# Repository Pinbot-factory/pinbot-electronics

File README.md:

**Pinbot** is an open-source platform for quickly building test jigs for electronics QA. The platform is made up of [mechanical fixture](https://github.com/Pinbot-factory/pinbot-mechanical), control electronics (this repo), jig-level software and backend to store all test results.

## Pinbot electronics
This repo is dedicated for electronics of a typical Pinbot jig. At a moment it is a compact carrier board for Raspberry Pi Zero [2](https://www.jeffgeerling.com/blog/2021/look-inside-raspberry-pi-zero-2-w-and-rp3a0-au/). The board also can be used with regular size RPis thru HAT connector (J3).

**It features:**
- 16 channels GPIO (0-24V) thru TCA9535
- 8 channels ADC (12 bit, 0-24V) thru ADS1015
- 4 signal relays
- USB hub
    - 4 downstream ports (3 USB-A + 1 as a pins on J2)
    - Per-port power control
    - Per-port fault signals for error and power failures handling
- Qwiic connector for easy I2C expansion
- Raspberry Pi 40-pin GPIO header with SPI, I2C, UART, etc
- USB-C for power supply
- User leds, test points, basic signal lines protection and more.

Carrier board is 114x65mm to fit perfectly into [Pinbot's chassis](https://github.com/Pinbot-factory/pinbot-mechanical/tree/main/chassis). You can use it as a test engine for a small projects and supply them (as well as connected USB periphery) with 5V.

The repo includes KiCAD source files, generated gerbers, BOM, and everything to produce it on your own. Python *library and software examples* are also available and briefly [documented](sw_examples/README.md).

## License
- [GNU GPLv3](https://www.gnu.org/licenses/gpl-3.0.en.html) for **software**: firmware, libraries, generators, tools, examples, etc
- [CERN-OHL-S](https://cern-ohl.web.cern.ch/) for **hardware**: PCB schematic, layout, BOM, gerbers, 3D models, g-codes, etc.
- [CC BY-SA 4.0](https://creativecommons.org/licenses/by-sa/4.0/deed.en) is for docs, pictures, articles, video, assets, etc.

Pinbot projects structure may mix different sources and artifacts — check corresponding dirrectories for `LICENSE` file.

-----------
*This project is sponsored by [NLnet](https://nlnet.nl/) as a part of [NGI Zero Review](https://nlnet.nl/NGI0/review/) program.*
<p align="left">
    
</p>

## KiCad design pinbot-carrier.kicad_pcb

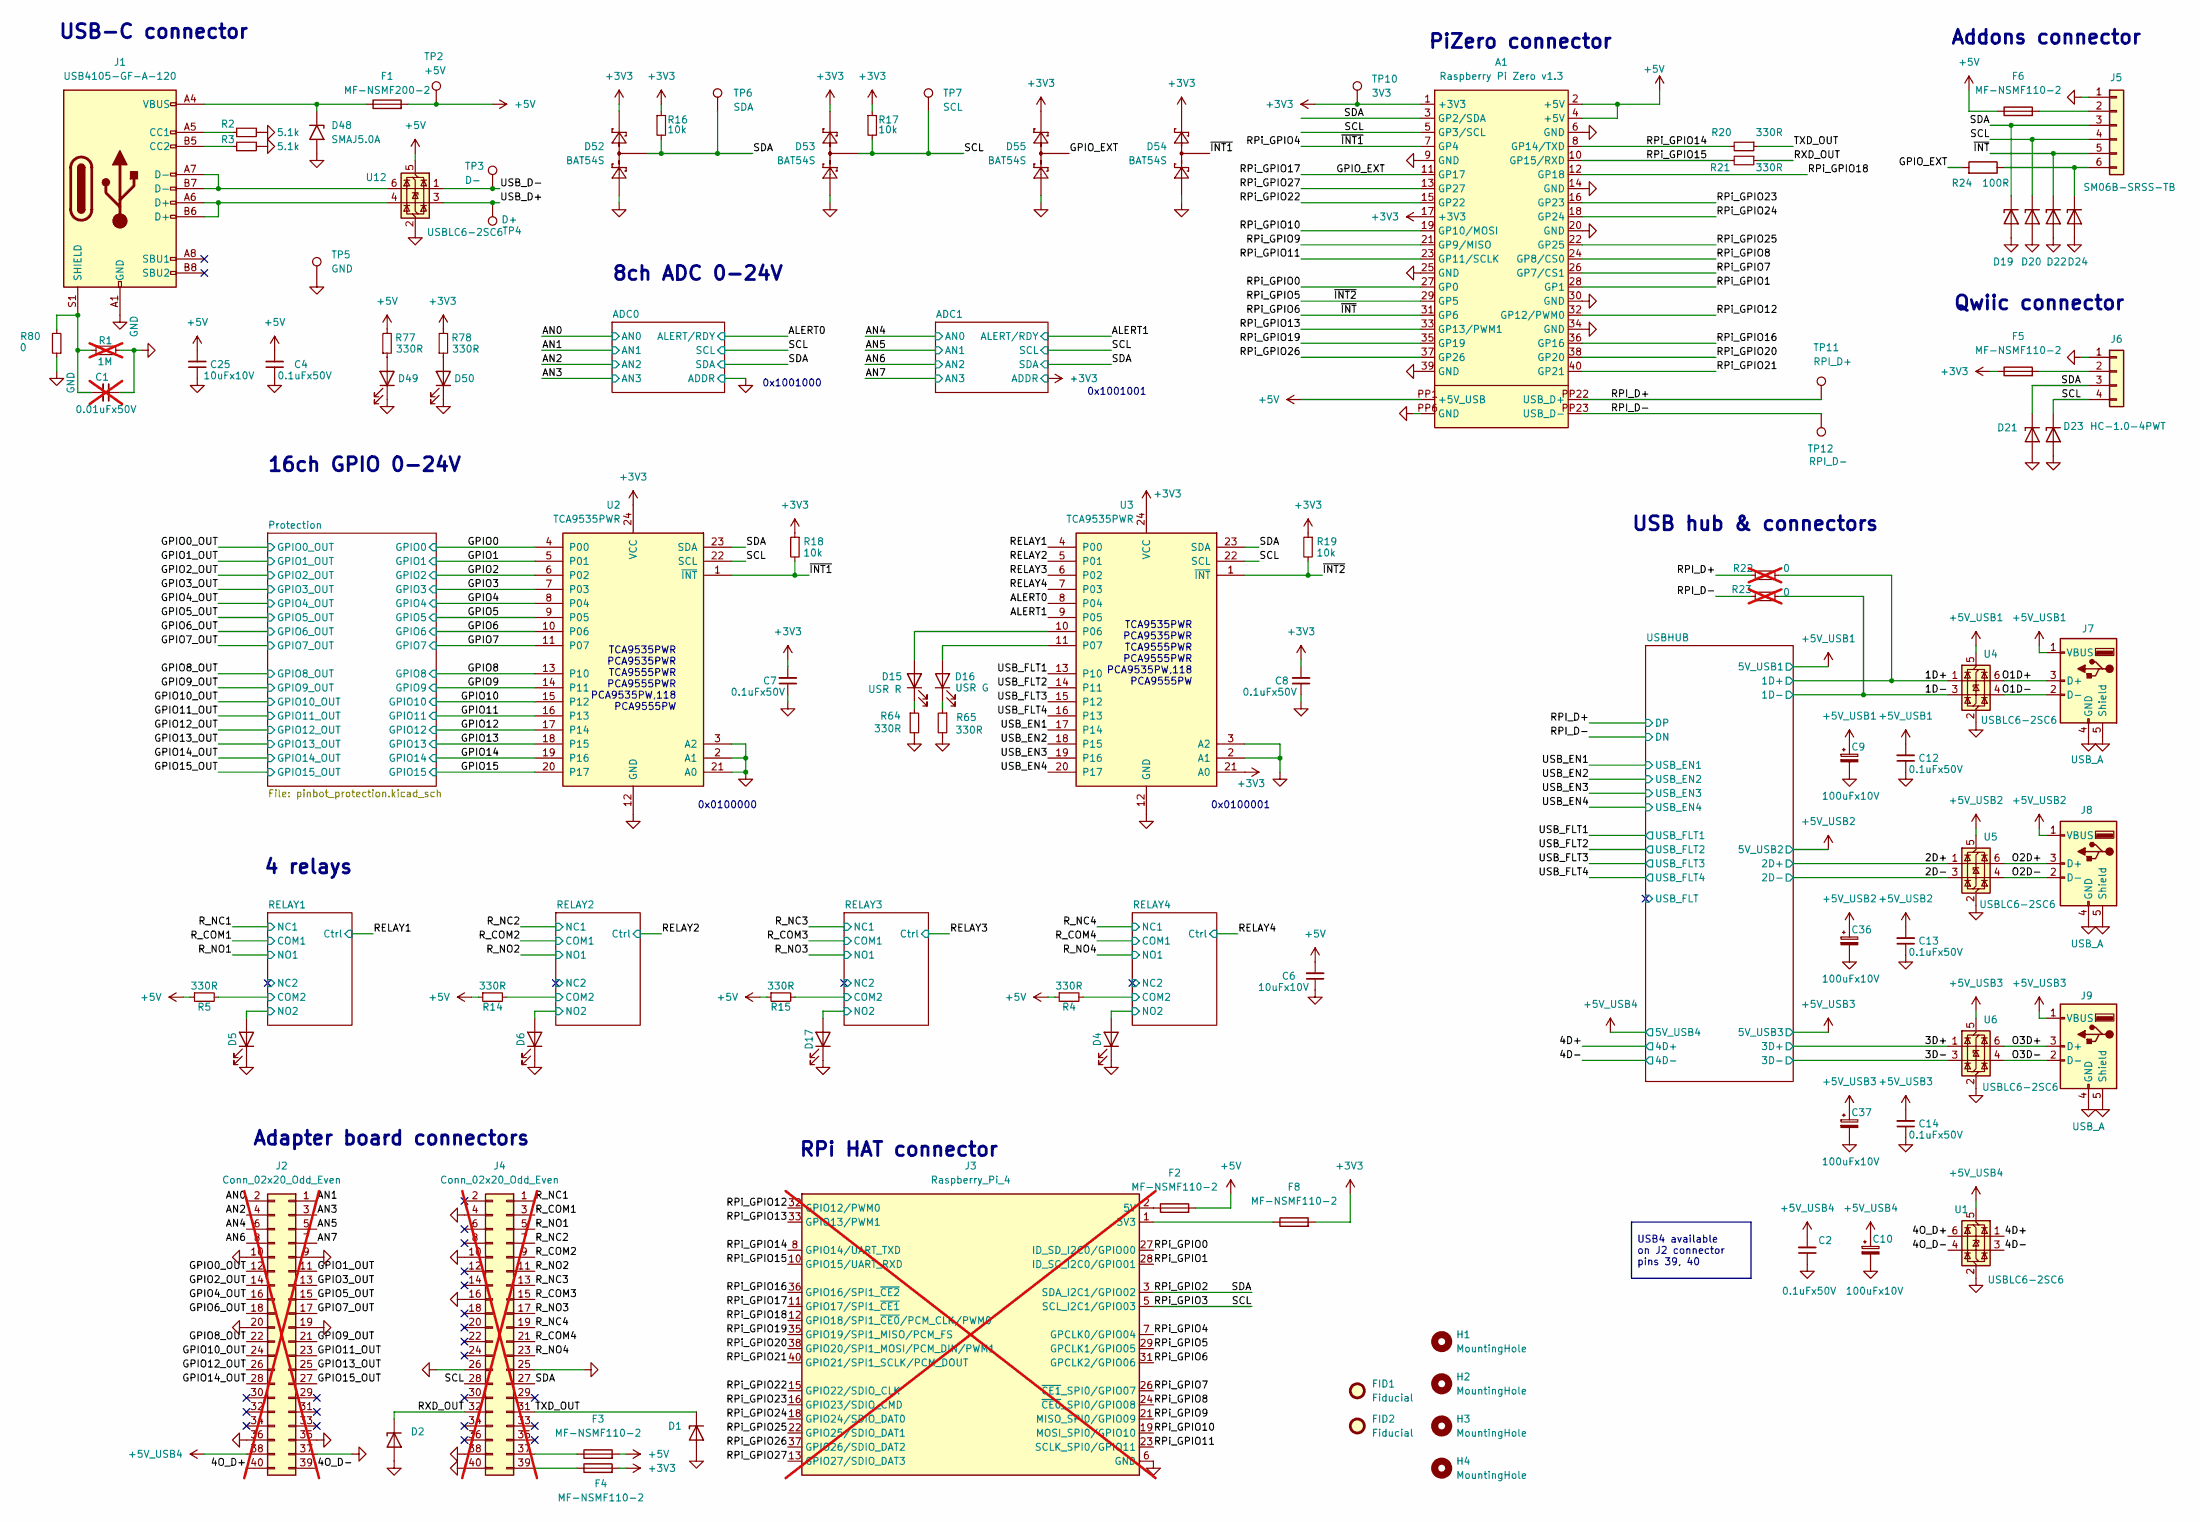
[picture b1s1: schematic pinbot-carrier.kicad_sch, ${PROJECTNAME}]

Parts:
A1: Raspberry Pi Zero v1.3; RASPI_ZERO_FULL; LCSC Part # C2977589
C1: 0.01uFx50V; C_0603_1608Metric; Mouser Part # 06031C103K4T4A; LCSC Part # C100042; not fitted
C2, C4, C12, C13, C14: 0.1uFx50V; C_0603_1608Metric; Mouser Part # CGA3E2X7R1H104M080AA; LCSC Part # C282519
C6, C25: 10uFx10V; C_0603_1608Metric; Mouser Part # GRM188Z71A106MA73J; LCSC Part # C2959727
C7, C8: 0.1uFx50V; C_0603_1608Metric; Mouser Part # CGA3E2X7R1H104M080AA
C9, C10, C36, C37: 100uFx10V; CP_EIA-3528-21_Kemet-B; LCSC Part # C600583
D1, D2, D19, D20, D21, D22, D23, D24: ESD5Z3.3T5G; D_SOD-523; Mouser Part # ESD5Z3.3T5G
D4, D5, D6, D17: 19-21/GHC-YR1S2/4T; LED_0603_1608Metric; LCSC Part # C2986048
D15: LTST-S270KRKT; LED_0603_1608Metric_side; Mouser Part # LTST-S270KRKT; LCSC Part # C125114
D16: LTST-S270KGKT; LED_0603_1608Metric_side; Mouser Part # LTST-S270KGKT; LCSC Part # C125113
D48: SMAJ5.0A; D_SMA; LCSC Part # C83329
D49, D50: XL-1608SURC-06; LED_0603_1608Metric; LCSC Part # C965799
D52, D53, D54, D55: BAT54S; SOT-23; LCSC Part # C19726
F1: MF-NSMF200-2; Fuse_1206_3216Metric; Mouser Part # MF-NSMF200-2; LCSC Part # C89656
F2, F3, F4, F5, F6, F8: MF-NSMF110-2; Fuse_1206_3216Metric; Mouser Part # MF-NSMF110-2; LCSC Part # C89654
FID1, FID2: Fiducial; Fiducial_1mm_Mask2mm
H1, H2, H3, H4: MountingHole; MountingHole_2.7mm
J1: USB4105-GF-A-120; USB_C_Receptacle_GCT_USB4105-xx-A_16P_TopMnt_Horizontal; Mouser Part # USB4105-GF-A-120
J2: Conn_02x20_Odd_Even; PinHeader_2x20_P2.54mm_Horizontal; LCSC Part # C124369; not fitted
J3: Raspberry_Pi_4; PinHeader_2x20_P2.54mm_Vertical; Manufacturer Part P125-1220A0BS116A1; LCSC Part # C19190512; not fitted
J4: Conn_02x20_Odd_Even; PinHeader_2x20_P2.54mm_Vertical; LCSC Part # C19190512; not fitted
J5: SM06B-SRSS-TB; JST_SM06B-SRSS-TB; Mouser Part # 10147606-00006LF; LCSC Part # C160405
J6: HC-1.0-4PWT; JST_SH_SM04B-SRSS-TB_1x04-1MP_P1.00mm_Horizontal; Mouser Part # 10147606-00004LF; LCSC Part # C2845363
J7, J8, J9: USB_A; GCT_USB1125-GF-B_REVA; Mouser Part # USB1125-GF-B
R1: 1M; R_0603_1608Metric; Mouser Part # ASC0603-1M0FT5; LCSC Part # C107698; not fitted
R2, R3: 5.1k; R_0603_1608Metric; Mouser Part # ERJ-3EKF5101V; LCSC Part # C2907114
R4, R5, R14, R15, R20, R21, R64, R65, R77, R78: 330R; R_0603_1608Metric; Mouser Part # RMCF0603FT330R; LCSC Part # C23138
R16, R17, R18, R19: 10k; R_0603_1608Metric; Mouser Part # RMC1/16K1002DTP; LCSC Part # C98220
R22, R23: 0; R_0603_1608Metric; Mouser Part # ERJ-3EKF5101V; LCSC Part # C95177; not fitted
R24: 100R; R_0603_1608Metric; Mouser Part # CRT0603-DY-1000ELF; LCSC Part # C2907089
R80: 0; R_0603_1608Metric; Mouser Part # ERJ-3EKF5101V; LCSC Part # C95177
TP2: +5V; TestPoint_Loop_D1.80mm_Drill1.0mm_Beaded
TP3: D-; TestPoint_Loop_D1.80mm_Drill1.0mm_Beaded
TP4: D+; TestPoint_Loop_D1.80mm_Drill1.0mm_Beaded
TP5: GND; TestPoint_Loop_D1.80mm_Drill1.0mm_Beaded
TP6: SDA; TestPoint_Loop_D1.80mm_Drill1.0mm_Beaded
TP7: SCL; TestPoint_Loop_D1.80mm_Drill1.0mm_Beaded
TP10: 3V3; TestPoint_Loop_D1.80mm_Drill1.0mm_Beaded
TP11: RPI_D+; TestPoint_Loop_D1.80mm_Drill1.0mm_Beaded
TP12: RPI_D-; TestPoint_Loop_D1.80mm_Drill1.0mm_Beaded
U1, U4, U5, U6, U12: USBLC6-2SC6; SOT-23-6; Mouser Part # USBLC6-2SC6
U2, U3: TCA9535PWR; TSSOP-24_4.4x7.8mm_P0.65mm; Mouser Part # TCA9535PWR

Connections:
+3V3: A1.1 (+3V3), A1.17 (+3V3), C7.2, C8.2, D52.2 (K), D53.2 (K), D54.2 (K), D55.2 (K), F4.2, F5.1, F8.2, R16.1, R17.1, R18.1, R19.1, R78.2, TP10.1 (1_1), U2.24 (VCC), U3.21 (A0), U3.24 (VCC); also elsewhere on the board
+5V: A1.2 (+5V), A1.4 (+5V), A1.PP1 (+5V_USB), C4.2, C6.2, C25.2, F1.2, F2.2, F3.2, F6.1, R4.1, R5.1, R14.1, R15.1, R77.2, TP2.1 (1_1), U12.5 (VBUS); also elsewhere on the board
+5V_USB1: C9.1, C12.2, J7.1 (VBUS), U4.5 (VBUS); also elsewhere on the board
+5V_USB2: C13.2, C36.1, J8.1 (VBUS), U5.5 (VBUS); also elsewhere on the board
+5V_USB3: C14.2, C37.1, J9.1 (VBUS), U6.5 (VBUS); also elsewhere on the board
+5V_USB4: C2.2, C10.1, J2.38, U1.5 (VBUS); also elsewhere on the board
/1D+: R22.2, U4.1 (I/O1); also elsewhere on the board
/1D-: R23.2, U4.3 (I/O2); also elsewhere on the board
/2D+: U5.1 (I/O1); also elsewhere on the board
/2D-: U5.3 (I/O2); also elsewhere on the board
/3D+: U6.1 (I/O1); also elsewhere on the board
/3D-: U6.3 (I/O2); also elsewhere on the board
/4D+: U1.1 (I/O1); also elsewhere on the board
/4D-: U1.3 (I/O2); also elsewhere on the board
/4O_D+: J2.40, U1.6 (I/O1)
/4O_D-: J2.39, U1.4 (I/O2)
/ALERT0: U3.8 (P04); also elsewhere on the board
/ALERT1: U3.9 (P05); also elsewhere on the board
/AN0: J2.2; also elsewhere on the board
/AN1: J2.1; also elsewhere on the board
/AN2: J2.4; also elsewhere on the board
/AN3: J2.3; also elsewhere on the board
/AN4: J2.6; also elsewhere on the board
/AN5: J2.5; also elsewhere on the board
/AN6: J2.8; also elsewhere on the board
/AN7: J2.7; also elsewhere on the board
/GPIO0: U2.4 (P00); also elsewhere on the board
/GPIO0_OUT: J2.12; also elsewhere on the board
/GPIO1: U2.5 (P01); also elsewhere on the board
/GPIO1_OUT: J2.11; also elsewhere on the board
/GPIO2: U2.6 (P02); also elsewhere on the board
/GPIO2_OUT: J2.14; also elsewhere on the board
/GPIO3: U2.7 (P03); also elsewhere on the board
/GPIO3_OUT: J2.13; also elsewhere on the board
/GPIO4: U2.8 (P04); also elsewhere on the board
/GPIO4_OUT: J2.16; also elsewhere on the board
/GPIO5: U2.9 (P05); also elsewhere on the board
/GPIO5_OUT: J2.15; also elsewhere on the board
/GPIO6: U2.10 (P06); also elsewhere on the board
/GPIO6_OUT: J2.18; also elsewhere on the board
/GPIO7: U2.11 (P07); also elsewhere on the board
/GPIO7_OUT: J2.17; also elsewhere on the board
/GPIO8: U2.13 (P10); also elsewhere on the board
/GPIO8_OUT: J2.22; also elsewhere on the board
/GPIO9: U2.14 (P11); also elsewhere on the board
/GPIO9_OUT: J2.21; also elsewhere on the board
/GPIO10: U2.15 (P12); also elsewhere on the board
/GPIO10_OUT: J2.24; also elsewhere on the board
/GPIO11: U2.16 (P13); also elsewhere on the board
/GPIO11_OUT: J2.23; also elsewhere on the board
/GPIO12: U2.17 (P14); also elsewhere on the board
/GPIO12_OUT: J2.26; also elsewhere on the board
/GPIO13: U2.18 (P15); also elsewhere on the board
/GPIO13_OUT: J2.25; also elsewhere on the board
/GPIO14: U2.19 (P16); also elsewhere on the board
/GPIO14_OUT: J2.28; also elsewhere on the board
/GPIO15: U2.20 (P17); also elsewhere on the board
/GPIO15_OUT: J2.27; also elsewhere on the board
/GPIO_EXT: A1.11 (GP17), D55.3 (COM), J3.11 (GPIO17/SPI1_~CE1), R24.2
/O1D+: J7.3 (D+), U4.6 (I/O1)
/O1D-: J7.2 (D-), U4.4 (I/O2)
/O2D+: J8.3 (D+), U5.6 (I/O1)
/O2D-: J8.2 (D-), U5.4 (I/O2)
/O3D+: J9.3 (D+), U6.6 (I/O1)
/O3D-: J9.2 (D-), U6.4 (I/O2)
/RELAY1: U3.4 (P00); also elsewhere on the board
/RELAY1/COM2: R5.2; also elsewhere on the board
/RELAY1/NO2: D5.2 (A); also elsewhere on the board
/RELAY2: U3.5 (P01); also elsewhere on the board
/RELAY2/COM2: R14.2; also elsewhere on the board
/RELAY2/NO2: D6.2 (A); also elsewhere on the board
/RELAY3: U3.6 (P02); also elsewhere on the board
/RELAY3/COM2: R15.2; also elsewhere on the board
/RELAY3/NO2: D17.2 (A); also elsewhere on the board
/RELAY4: U3.7 (P03); also elsewhere on the board
/RELAY4/COM2: R4.2; also elsewhere on the board
/RELAY4/NO2: D4.2 (A); also elsewhere on the board
/RPI_D+: A1.PP22 (USB_D+), R22.1, TP11.1 (1_1); also elsewhere on the board
/RPI_D-: A1.PP23 (USB_D-), R23.1, TP12.1 (1_1); also elsewhere on the board
/RPi_GPIO0: A1.27 (GP0), J3.27 (ID_SD_I2C0/GPIO00)
/RPi_GPIO1: A1.28 (GP1), J3.28 (ID_SC_I2C0/GPIO01)
/RPi_GPIO2: A1.3 (GP2/SDA), D19.1 (K), D21.1 (K), D52.3 (COM), J3.3 (SDA_I2C1/GPIO02), J4.27, J5.3, J6.3, R16.2, TP6.1 (1_1), U2.23 (SDA), U3.23 (SDA); also elsewhere on the board
/RPi_GPIO3: A1.5 (GP3/SCL), D20.1 (K), D23.1 (K), D53.3 (COM), J3.5 (SCL_I2C1/GPIO03), J4.28, J5.4, J6.4, R17.2, TP7.1 (1_1), U2.22 (SCL), U3.22 (SCL); also elsewhere on the board
/RPi_GPIO4: A1.7 (GP4), D54.3 (COM), J3.7 (GPCLK0/GPIO04), R18.2, U2.1 (~INT)
/RPi_GPIO5: A1.29 (GP5), J3.29 (GPCLK1/GPIO05), R19.2, U3.1 (~INT)
/RPi_GPIO6: A1.31 (GP6), D22.1 (K), J3.31 (GPCLK2/GPIO06), J5.5
/RPi_GPIO7: A1.26 (GP7/CS1), J3.26 (~CE1_SPI0/GPIO07)
/RPi_GPIO8: A1.24 (GP8/CS0), J3.24 (~CE0_SPI0/GPIO08)
/RPi_GPIO9: A1.21 (GP9/MISO), J3.21 (MISO_SPI0/GPIO09)
/RPi_GPIO10: A1.19 (GP10/MOSI), J3.19 (MOSI_SPI0/GPIO10)
/RPi_GPIO11: A1.23 (GP11/SCLK), J3.23 (SCLK_SPI0/GPIO11)
/RPi_GPIO12: A1.32 (GP12/PWM0), J3.32 (GPIO12/PWM0)
/RPi_GPIO13: A1.33 (GP13/PWM1), J3.33 (GPIO13/PWM1)
/RPi_GPIO14: A1.8 (GP14/TXD), J3.8 (GPIO14/UART_TXD), R20.2
/RPi_GPIO15: A1.10 (GP15/RXD), J3.10 (GPIO15/UART_RXD), R21.2
/RPi_GPIO16: A1.36 (GP16), J3.36 (GPIO16/SPI1_~CE2)
/RPi_GPIO18: A1.12 (GP18), J3.12 (GPIO18/SPI1_~CE0/PCM_CLK/PWM0)
/RPi_GPIO19: A1.35 (GP19), J3.35 (GPIO19/SPI1_MISO/PCM_FS)
/RPi_GPIO20: A1.38 (GP20), J3.38 (GPIO20/SPI1_MOSI/PCM_DIN/PWM1)
/RPi_GPIO21: A1.40 (GP21), J3.40 (GPIO21/SPI1_SCLK/PCM_DOUT)
/RPi_GPIO22: A1.15 (GP22), J3.15 (GPIO22/SDIO_CLK)
/RPi_GPIO23: A1.16 (GP23), J3.16 (GPIO23/SDIO_CMD)
/RPi_GPIO24: A1.18 (GP24), J3.18 (GPIO24/SDIO_DAT0)
/RPi_GPIO25: A1.22 (GP25), J3.22 (GPIO25/SDIO_DAT1)
/RPi_GPIO26: A1.37 (GP26), J3.37 (GPIO26/SDIO_DAT2)
/RPi_GPIO27: A1.13 (GP27), J3.13 (GPIO27/SDIO_DAT3)
/RXD_OUT: D2.1 (K), J4.32, R21.1
/R_COM1: J4.3; also elsewhere on the board
/R_COM2: J4.9; also elsewhere on the board
/R_COM3: J4.15; also elsewhere on the board
/R_COM4: J4.21; also elsewhere on the board
/R_NC1: J4.1; also elsewhere on the board
/R_NC2: J4.7; also elsewhere on the board
/R_NC3: J4.13; also elsewhere on the board
/R_NC4: J4.19; also elsewhere on the board
/R_NO1: J4.5; also elsewhere on the board
/R_NO2: J4.11; also elsewhere on the board
/R_NO3: J4.17; also elsewhere on the board
/R_NO4: J4.23; also elsewhere on the board
/TXD_OUT: D1.1 (K), J4.31, R20.1
/USB_D+: TP4.1 (1_1), U12.3 (I/O2)
/USB_D-: TP3.1 (1_1), U12.1 (I/O1)
/USB_EN1: U3.17 (P14); also elsewhere on the board
/USB_EN2: U3.18 (P15); also elsewhere on the board
/USB_EN3: U3.19 (P16); also elsewhere on the board
/USB_EN4: U3.20 (P17); also elsewhere on the board
/USB_FLT1: U3.13 (P10); also elsewhere on the board
/USB_FLT2: U3.14 (P11); also elsewhere on the board
/USB_FLT3: U3.15 (P12); also elsewhere on the board
/USB_FLT4: U3.16 (P13); also elsewhere on the board
GND: A1.6 (GND), A1.9 (GND), A1.14 (GND), A1.20 (GND), A1.25 (GND), A1.30 (GND), A1.34 (GND), A1.39 (GND), A1.PP6 (GND), C1.1, C2.1, C4.1, C6.1, C7.1, C8.1, C9.2, C10.2, C12.1, C13.1, C14.1, C25.1, C36.2, C37.2, D1.2 (A), D2.2 (A), D4.1 (K), D5.1 (K), D6.1 (K), D17.1 (K), D19.2 (A), D20.2 (A), D21.2 (A), D22.2 (A), D23.2 (A), D24.2 (A), D48.2 (A2), D49.1 (K), D50.1 (K), D52.1 (A), D53.1 (A), D54.1 (A), D55.1 (A), J1.A1 (GND), J1.A12 (GND), J1.B1 (GND), J1.B12 (GND), J2.9, J2.10, J2.19, J2.20, J2.35, J2.36, J2.37, J3.6 (GND), J3.9 (GND), J3.14 (GND), J3.20 (GND), J3.25 (GND), J3.30 (GND), J3.34 (GND), J3.39 (GND), J4.4, J4.10, J4.16, J4.25, J4.26, J4.38, J4.40, J5.1, J6.1, J7.4 (GND), J7.5 (Shield), J8.4 (GND), J8.5 (Shield), J9.4 (GND), J9.5 (Shield), R1.2, R2.2, R3.2, R64.2, R65.2, R80.1, TP5.1 (1_1), U1.2 (GND), U2.2 (A1), U2.3 (A2), U2.12 (GND), U2.21 (A0), U3.2 (A1), U3.3 (A2), U3.12 (GND), U4.2 (GND), U5.2 (GND), U6.2 (GND), U12.2 (GND); also elsewhere on the board
unnamed: D15.2 (A), U3.10 (P06)
unnamed: D15.1 (K), R64.1
unnamed: D16.2 (A), U3.11 (P07)
unnamed: D16.1 (K), R65.1
unnamed: D24.1 (K), J5.6, R24.1
unnamed: D48.1 (A1), F1.1, J1.A4 (VBUS), J1.A9 (VBUS), J1.B4 (VBUS), J1.B9 (VBUS)
unnamed: D49.2 (A), R77.1
unnamed: D50.2 (A), R78.1
unnamed: F2.1, J3.2 (5V), J3.4 (5V)
unnamed: F8.1, J3.1 (3V3), J3.17 (3V3)
unnamed: J1.A5 (CC1), R2.1
unnamed: J1.B5 (CC2), R3.1
unnamed: J1.A6 (D+), J1.B6 (D+), U12.4 (I/O2)
unnamed: J1.A7 (D-), J1.B7 (D-), U12.6 (I/O1)
unnamed: C1.2, J1.S1 (SHIELD), R1.1, R80.2
unnamed: F3.1, J4.37
unnamed: F4.1, J4.39
unnamed: F6.2, J5.2
unnamed: F5.2, J6.2

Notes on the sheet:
PiZero connector
0x1001000
USB-C connector
0x0100000
0x1001001
4 relays
0x0100001
8ch ADC 0-24V
Qwiic connector
TCA9535PWR PCA9535PWR TCA9555PWR PCA9555PWR PCA9535PW,118 PCA9555PW
Addons connector
RPi HAT connector
16ch GPIO 0-24V
USB hub & connectors
Adapter board connectors
USB4 available on J2 connector pins 39, 40

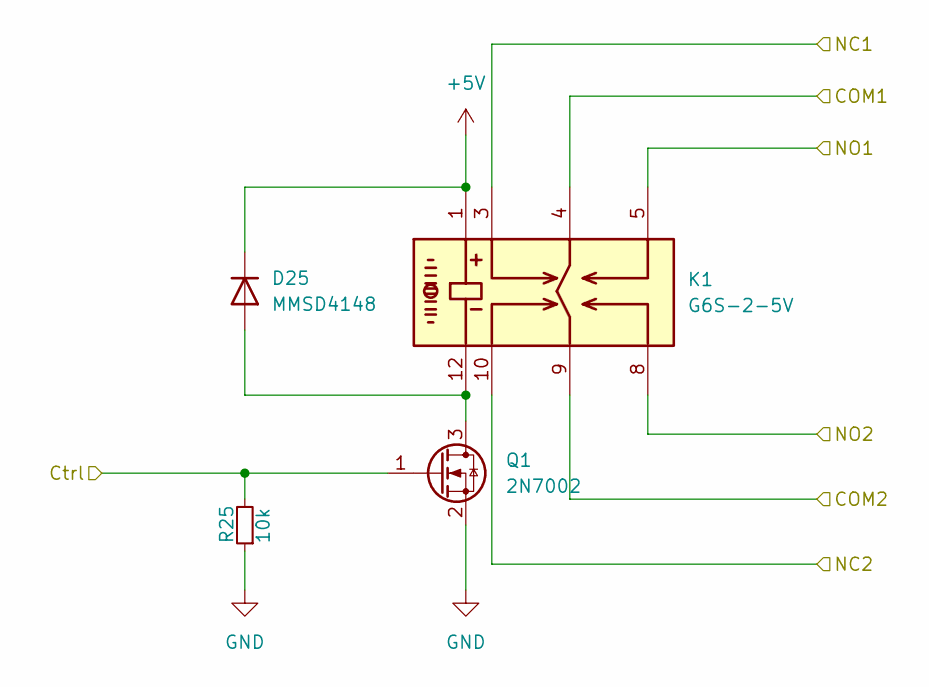
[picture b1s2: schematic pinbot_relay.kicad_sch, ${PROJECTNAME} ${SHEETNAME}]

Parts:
D25: MMSD4148; D_SOD-123; LCSC Part # C11177
K1: G6S-2-5V; Manufacturer Part G6S-2 DC5; LCSC Part # C32776
Q1: 2N7002; SOT-23; LCSC Part # C81445
R25: 10k; R_0603_1608Metric; Mouser Part # RMC1/16K1002DTP; LCSC Part # C98220

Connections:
+5V: D25.1 (K), K1.1; also elsewhere on the board
/RELAY4: Q1.1 (G), R25.2; also elsewhere on the board
/RELAY4/COM2: K1.9; also elsewhere on the board
/RELAY4/NC2: K1.10
/RELAY4/NO2: K1.8; also elsewhere on the board
/R_COM4: K1.4; also elsewhere on the board
/R_NC4: K1.3; also elsewhere on the board
/R_NO4: K1.5; also elsewhere on the board
GND: Q1.2 (S), R25.1; also elsewhere on the board
unnamed: D25.2 (A), K1.12, Q1.3 (D)

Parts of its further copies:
D26, D27, D28: MMSD4148; D_SOD-123; LCSC Part # C11177
K2, K3, K4: G6S-2-5V; Manufacturer Part G6S-2 DC5; LCSC Part # C32776
Q2, Q3, Q4: 2N7002; SOT-23; LCSC Part # C81445
R44, R45, R46: 10k; R_0603_1608Metric; Mouser Part # RMC1/16K1002DTP; LCSC Part # C98220

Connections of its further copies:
+5V: D26.1 (K), D27.1 (K), D28.1 (K), K2.1, K3.1, K4.1; also elsewhere on the board
/RELAY1: Q2.1 (G), R44.2; also elsewhere on the board
/RELAY1/COM2: K2.9; also elsewhere on the board
/RELAY1/NC2: K2.10
/RELAY1/NO2: K2.8; also elsewhere on the board
/RELAY2: Q3.1 (G), R45.2; also elsewhere on the board
/RELAY2/COM2: K3.9; also elsewhere on the board
/RELAY2/NC2: K3.10
/RELAY2/NO2: K3.8; also elsewhere on the board
/RELAY3: Q4.1 (G), R46.2; also elsewhere on the board
/RELAY3/COM2: K4.9; also elsewhere on the board
/RELAY3/NC2: K4.10
/RELAY3/NO2: K4.8; also elsewhere on the board
/R_COM1: K2.4; also elsewhere on the board
/R_COM2: K3.4; also elsewhere on the board
/R_COM3: K4.4; also elsewhere on the board
/R_NC1: K2.3; also elsewhere on the board
/R_NC2: K3.3; also elsewhere on the board
/R_NC3: K4.3; also elsewhere on the board
/R_NO1: K2.5; also elsewhere on the board
/R_NO2: K3.5; also elsewhere on the board
/R_NO3: K4.5; also elsewhere on the board
GND: Q2.2 (S), Q3.2 (S), Q4.2 (S), R44.1, R45.1, R46.1; also elsewhere on the board
unnamed: D26.2 (A), K2.12, Q2.3 (D)
unnamed: D27.2 (A), K3.12, Q3.3 (D)
unnamed: D28.2 (A), K4.12, Q4.3 (D)

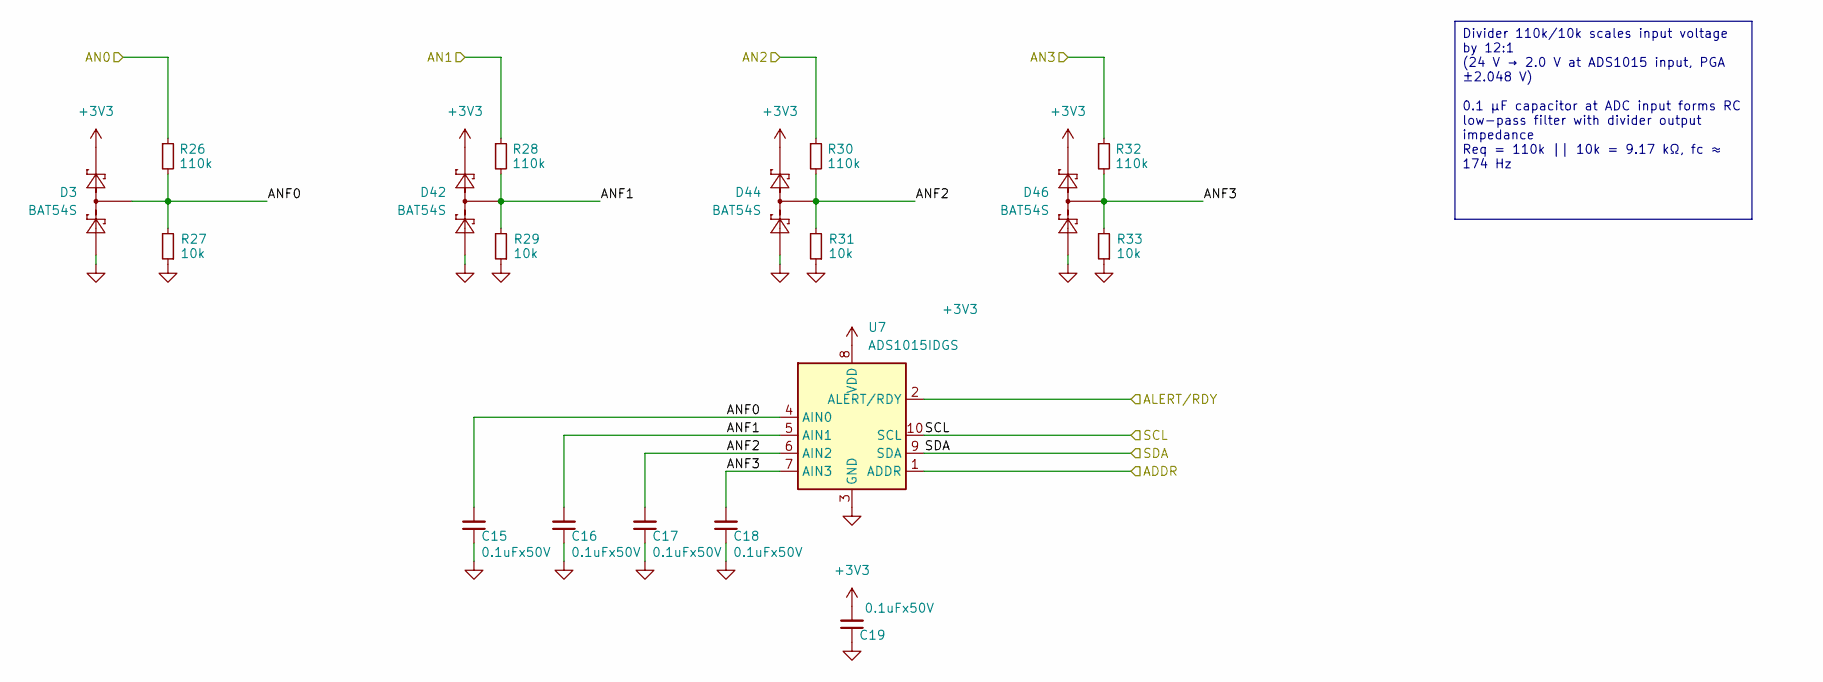
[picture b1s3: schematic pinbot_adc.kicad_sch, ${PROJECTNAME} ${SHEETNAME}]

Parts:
C15, C16, C17, C18, C19: 0.1uFx50V; C_0603_1608Metric; Mouser Part # CGA3E2X7R1H104M080AA; LCSC Part # C282519
D3, D42, D44, D46: BAT54S; SOT-23; LCSC Part # C19726
R26, R28, R30, R32: 110k; R_0603_1608Metric; Tolerance 1%; LCSC Part # C25805
R27, R29, R31, R33: 10k; R_0603_1608Metric; Tolerance 1%; Mouser Part # RMC1/16K1002DTP; LCSC Part # C98220
U7: ADS1015IDGS; TSSOP-10_3x3mm_P0.5mm; Mouser Part # ADS1015IDGS

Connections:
+3V3: C19.2, D3.2 (K), D42.2 (K), D44.2 (K), D46.2 (K), U7.8 (VDD); also elsewhere on the board
/ADC0/ANF0: C15.2, D3.3 (COM), R26.2, R27.2, U7.4 (AIN0)
/ADC0/ANF1: C16.2, D42.3 (COM), R28.2, R29.2, U7.5 (AIN1)
/ADC0/ANF2: C17.2, D44.3 (COM), R30.2, R31.2, U7.6 (AIN2)
/ADC0/ANF3: C18.2, D46.3 (COM), R32.2, R33.2, U7.7 (AIN3)
/ALERT0: U7.2 (ALERT/RDY); also elsewhere on the board
/AN0: R26.1; also elsewhere on the board
/AN1: R28.1; also elsewhere on the board
/AN2: R30.1; also elsewhere on the board
/AN3: R32.1; also elsewhere on the board
/RPi_GPIO2: U7.9 (SDA); also elsewhere on the board
/RPi_GPIO3: U7.10 (SCL); also elsewhere on the board
GND: C15.1, C16.1, C17.1, C18.1, C19.1, D3.1 (A), D42.1 (A), D44.1 (A), D46.1 (A), R27.1, R29.1, R31.1, R33.1, U7.1 (ADDR), U7.3 (GND); also elsewhere on the board

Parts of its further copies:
C20, C21, C22, C23, C24: 0.1uFx50V; C_0603_1608Metric; Mouser Part # CGA3E2X7R1H104M080AA; LCSC Part # C282519
D31, D43, D45, D47: BAT54S; SOT-23; LCSC Part # C19726
R35, R37, R39, R41: 110k; R_0603_1608Metric; Tolerance 1%; LCSC Part # C25805
R36, R38, R40, R42: 10k; R_0603_1608Metric; Tolerance 1%; Mouser Part # RMC1/16K1002DTP; LCSC Part # C98220
U8: ADS1015IDGS; TSSOP-10_3x3mm_P0.5mm; Mouser Part # ADS1015IDGS

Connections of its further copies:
+3V3: C24.2, D31.2 (K), D43.2 (K), D45.2 (K), D47.2 (K), U8.1 (ADDR), U8.8 (VDD); also elsewhere on the board
/ADC1/ANF0: C20.2, D31.3 (COM), R35.2, R36.2, U8.4 (AIN0)
/ADC1/ANF1: C21.2, D43.3 (COM), R37.2, R38.2, U8.5 (AIN1)
/ADC1/ANF2: C22.2, D45.3 (COM), R39.2, R40.2, U8.6 (AIN2)
/ADC1/ANF3: C23.2, D47.3 (COM), R41.2, R42.2, U8.7 (AIN3)
/ALERT1: U8.2 (ALERT/RDY); also elsewhere on the board
/AN4: R35.1; also elsewhere on the board
/AN5: R37.1; also elsewhere on the board
/AN6: R39.1; also elsewhere on the board
/AN7: R41.1; also elsewhere on the board
/RPi_GPIO2: U8.9 (SDA); also elsewhere on the board
/RPi_GPIO3: U8.10 (SCL); also elsewhere on the board
GND: C20.1, C21.1, C22.1, C23.1, C24.1, D31.1 (A), D43.1 (A), D45.1 (A), D47.1 (A), R36.1, R38.1, R40.1, R42.1, U8.3 (GND); also elsewhere on the board

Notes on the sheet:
Divider 110k/10k scales input voltage by 12:1 (24 V → 2.0 V at ADS1015 input, PGA ±2.048 V) 0.1 µF capacitor at ADC input forms RC low-pass filter with divider output impedance Req = 110k || 10k = 9.17 kΩ, fc ≈ 174 Hz

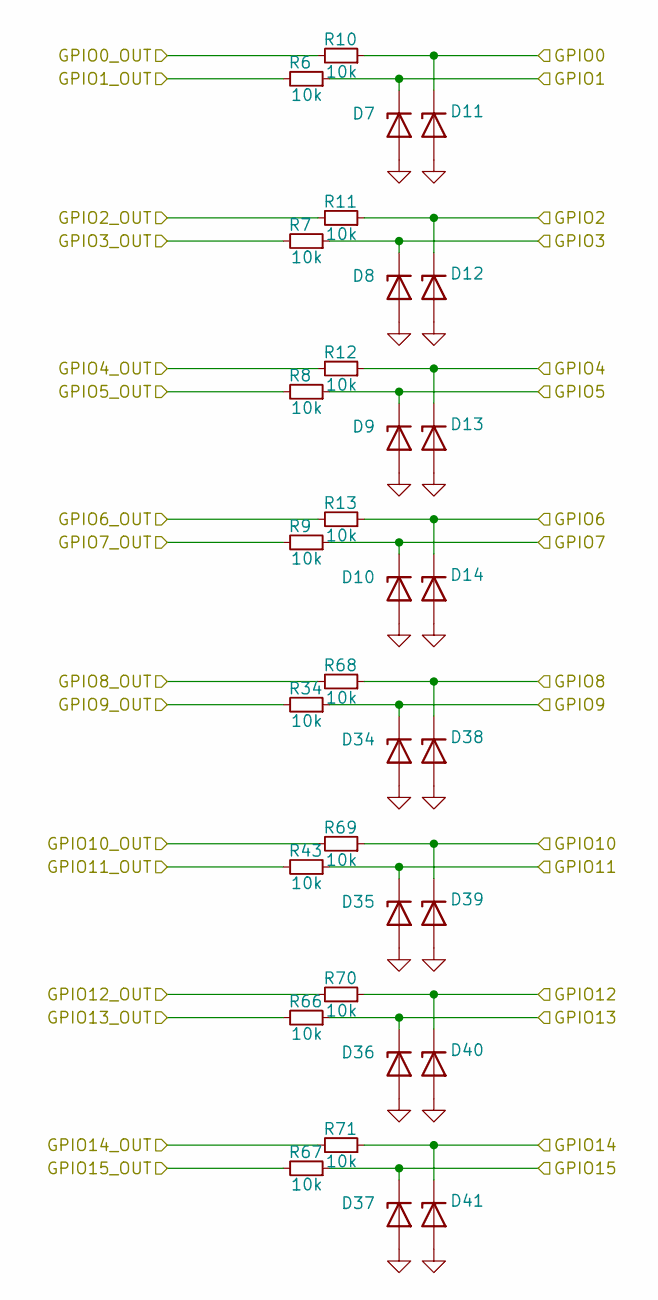
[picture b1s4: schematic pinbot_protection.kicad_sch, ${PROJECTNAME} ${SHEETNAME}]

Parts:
D7, D8, D9, D10, D11, D12, D13, D14, D34, D35, D36, D37, D38, D39, D40, D41: ESD5Z3.3T5G; D_SOD-523; Mouser Part # ESD5Z3.3T5G
R6, R7, R8, R9, R10, R11, R12, R13, R34, R43, R66, R67, R68, R69, R70, R71: 10k; R_0603_1608Metric; Mouser Part # RMC1/16K1002DTP; LCSC Part # C98220

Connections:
/GPIO0: D11.1 (K), R10.1; also elsewhere on the board
/GPIO0_OUT: R10.2; also elsewhere on the board
/GPIO1: D7.1 (K), R6.1; also elsewhere on the board
/GPIO1_OUT: R6.2; also elsewhere on the board
/GPIO2: D12.1 (K), R11.1; also elsewhere on the board
/GPIO2_OUT: R11.2; also elsewhere on the board
/GPIO3: D8.1 (K), R7.1; also elsewhere on the board
/GPIO3_OUT: R7.2; also elsewhere on the board
/GPIO4: D13.1 (K), R12.1; also elsewhere on the board
/GPIO4_OUT: R12.2; also elsewhere on the board
/GPIO5: D9.1 (K), R8.1; also elsewhere on the board
/GPIO5_OUT: R8.2; also elsewhere on the board
/GPIO6: D14.1 (K), R13.1; also elsewhere on the board
/GPIO6_OUT: R13.2; also elsewhere on the board
/GPIO7: D10.1 (K), R9.1; also elsewhere on the board
/GPIO7_OUT: R9.2; also elsewhere on the board
/GPIO8: D38.1 (K), R68.1; also elsewhere on the board
/GPIO8_OUT: R68.2; also elsewhere on the board
/GPIO9: D34.1 (K), R34.1; also elsewhere on the board
/GPIO9_OUT: R34.2; also elsewhere on the board
/GPIO10: D39.1 (K), R69.1; also elsewhere on the board
/GPIO10_OUT: R69.2; also elsewhere on the board
/GPIO11: D35.1 (K), R43.1; also elsewhere on the board
/GPIO11_OUT: R43.2; also elsewhere on the board
/GPIO12: D40.1 (K), R70.1; also elsewhere on the board
/GPIO12_OUT: R70.2; also elsewhere on the board
/GPIO13: D36.1 (K), R66.1; also elsewhere on the board
/GPIO13_OUT: R66.2; also elsewhere on the board
/GPIO14: D41.1 (K), R71.1; also elsewhere on the board
/GPIO14_OUT: R71.2; also elsewhere on the board
/GPIO15: D37.1 (K), R67.1; also elsewhere on the board
/GPIO15_OUT: R67.2; also elsewhere on the board
GND: D7.2 (A), D8.2 (A), D9.2 (A), D10.2 (A), D11.2 (A), D12.2 (A), D13.2 (A), D14.2 (A), D34.2 (A), D35.2 (A), D36.2 (A), D37.2 (A), D38.2 (A), D39.2 (A), D40.2 (A), D41.2 (A); also elsewhere on the board
